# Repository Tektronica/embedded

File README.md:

# embedded

Personal embedded projects in one repository: microcontroller firmware, Raspberry Pi Python
services, shared libraries, and the KiCad design packages for the custom boards.

## Layout

| Folder                 | Contents                                                                                                       |
| ---------------------- | -------------------------------------------------------------------------------------------------------------- |
| `projects/`            | Things built to be used. Code is in `fw/` (PlatformIO) or `python/`, and `hw/` holds the KiCad package for a custom PCB. |
| `examples/<platform>/` | Single-concept demos, one self-contained firmware project each                                                 |
| `lib/<platform>/`      | Shared libraries: `arduino` for firmware, `kicad` for the symbol library                                       |
| `tools/`               | Hardware release tools: board outputs, BOM merge, printable review checklist                                   |
| `orders/`              | One folder per Digi-Key or Mouser order, holding the BOM that was bought                                       |
| `docs/`                | Cross-project notes, including `docs/hw/` for board design, part selection, and review                         |

## Projects

| Project                                          | Platform              | Custom PCB | Description                                                                                                         |
| ------------------------------------------------ | --------------------- | ---------- | ------------------------------------------------------------------------------------------------------------------- |
| [led-dimmer-4ch](projects/led-dimmer-4ch/)       | Arduino Nano          | Yes        | Four pot-controlled LED channels driven by PT4115 buck LED drivers on 12 V                                          |
| [toy-microwave](projects/toy-microwave/)         | Arduino Nano          | Yes        | Toy microwave control panel: countdown, clock, kitchen timer, 16-key keypad, and 4-digit display through an ET6226M |
| [led-dimmer-ws2812](projects/led-dimmer-ws2812/) | Arduino Nano          | No         | N-channel pot dimmer driving a WS2812 LED strip                                                                     |
| [robot-buoy](projects/robot-buoy/)               | Arduino Nano          | No         | Vertical-profiling float that dives and surfaces with a syringe ballast                                             |
| [game-dino-run](projects/game-dino-run/)         | Arduino Nano          | No         | T-Rex-Run-style game on an OLED, with the score on a 7-segment display                                              |
| [weather-station](projects/weather-station/)     | Raspberry Pi / Python | No         | Sensor collector, read-only Flask dashboard, and daily email digest, as four separate Python packages               |

## Examples

| Example                                                                   | Platform     | Demonstrates                                                                           |
| ------------------------------------------------------------------------- | ------------ | -------------------------------------------------------------------------------------- |
| [buzzer-simple](examples/arduino-nano/buzzer-simple/)                     | Arduino Nano | A passive buzzer on a button press                                                     |
| [buzzer-patterns](examples/arduino-nano/buzzer-patterns/)                 | Arduino Nano | Three buttons, each playing a different non-blocking tone pattern                      |
| [buzzer-song](examples/arduino-nano/buzzer-song/)                         | Arduino Nano | Song playback from note tables                                                         |
| [keypad](examples/arduino-nano/keypad/)                                   | Arduino Nano | A debounced 4x4 matrix keypad reader                                                   |
| [seven-segment](examples/arduino-nano/seven-segment/)                     | Arduino Nano | A 4-digit 7-segment display with static, flashing, and rolling modes                   |
| [display-keyscan-et6226m](examples/arduino-nano/display-keyscan-et6226m/) | Arduino Nano | The ET6226M display and key-scan driver on its own                                     |
| [pwm-pot-demo](examples/arduino-nano/pwm-pot-demo/)                       | Arduino Nano | A potentiometer setting PWM duty                                                       |
| [stepper](examples/arduino-nano/stepper/)                                 | Arduino Nano | A potentiometer setting stepper motor speed                                            |
| [toy-microwave-tm1637](examples/arduino-nano/toy-microwave-tm1637/)       | Arduino Nano | The earlier toy microwave on a TM1637 display and membrane keypad, kept as a reference |

## Tooling

- VS Code with the PlatformIO extension, or the `pio` CLI. No Arduino IDE.
- KiCad 10 for the custom boards.
- Wokwi for simulating examples that include a `diagram.json`.
- Python 3.12 or newer for the Raspberry Pi projects. Each one documents its own setup.

## Getting started

1. Install PlatformIO. For a VS Code-only install, put the CLI on your path:
   `export PATH="$HOME/.platformio/penv/bin:$PATH"`
2. Build any firmware from the repo root: `pio run -d projects/toy-microwave/fw`
3. Run its native unit tests: `pio test -d projects/toy-microwave/fw -e native`
4. Run every shared library's tests: `for l in lib/arduino/*/; do pio test -d "$l"; done`
5. Regenerate a board's BOM, fab, and review outputs: `tools/release.sh projects/toy-microwave/hw`

Each project and example README covers its own hardware, pins, and behavior.

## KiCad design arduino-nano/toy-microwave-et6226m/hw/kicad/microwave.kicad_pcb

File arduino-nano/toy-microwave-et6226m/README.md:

# arduino-nano/toy-microwave-et6226m

Arduino Nano firmware for a toy/prop microwave oven control panel: a countdown timer on a 4-digit
display, a turntable motor, a done/alert buzzer, a cooling fan and buzzer-tone layer for the
running "hum," an interior light, and a matrix keypad for setting time, start/stop, and the
time-of-day clock shown while idle. Display rendering and keypad scanning both go through a
single UMW ET6226M chip over one two-wire bus, rather than a separate display driver chip plus a
bit-banged matrix scan — see `arduino-nano/toy-microwave-tm1637` for that earlier approach, frozen
as a reference once this project moved to the ET6226M.

## BOM

| Qty | Role (generic) | Part chosen | Notes |
|---|---|---|---|
| 1 | 4-digit 7-segment display | Kingbright CC56-12SURKWA, common cathode | Per `hw/kicad`'s schematic (`U2`). Driven entirely through the ET6226M -- no separate display driver chip. Must be common cathode: the ET6226M's SG pins source current and its GR pins sink it. Pin-for-pin with the CA56-12 footprint. |
| 1 | Display + keypad-scan driver | UMW ET6226M (SOP-16) | Per the schematic (`U5`). Two-wire CLK/DAT to the MCU; drives the display's 4 digits and scans the 16-key matrix, sharing its GR/SG lines with the display per the schematic's `SEG_x/ROWn` and `DIG_CAn/COLn` nets. Runs in `EightSegment` mode, since `DP/KP` is wired directly to the display's shared DP line, not into the key matrix. |
| 16 | Keyswitches | Cherry MX-style (`MX1`-`MX16` in the schematic) | Diode-per-key matrix (`D1`-`D16`), `SG1-4` as rows / `GR1-4` as columns -- the same 4x4 layout and key legends (`1-9,0,*,#,A-D`) as `toy-microwave-tm1637`'s membrane keypad, just wired through the ET6226M instead of directly to the MCU. |
| 1 | Buzzer (done/alert tone, button feedback, running hum) | 12085 buzzer, 12×8.5mm, 42Ω, 3–12V | Sold in a 20-pack. Passive, electromagnetic (the 42Ω is its coil) — driven via `tone()`/PWM; also layers a quiet low-frequency tone during Running, alongside the fan and motor, for the ambient hum. |
| 1 | Buzzer driver | AO3400A (`Q2`), 100Ω gate resistor (`R9`), SS14 flyback (`D18`) | Low-side switch: the coil draws ~119mA at 5V, over the ATmega328P's 40mA pin limit. `D18` clamps the coil's turn-off spike to `+5V`. |
| 1 | Turntable motor | TYC-50 synchronous motor, 12V DC, 5–6 RPM, CW/CCW, 4W | Matches a real microwave turntable's rotation speed; its own running sound also contributes to the hum. |
| 1 | Cooling fan (running hum) | Generic 12V DC brushless fan, 40×40×10mm, sleeve bearing, ~0.08A | A commodity spec, not a specific listing — any 12V 40mm fan matches. Matches the 12V rail already used by the motor/light rather than introducing a separate 5V domain. Needs a transistor/MOSFET driver, same as the motor — not a direct GPIO connection. |
| 1 | Interior/status light | 80mm white COB LED ring ("angel eye" halo ring) | Sold in a 2-pack. 12V/24V rated — confirm current draw and how it's switched (relay/MOSFET vs. direct GPIO) before wiring. |

Motor, fan, and light are reserved, not wired. `CTRL_MOTOR`/`CTRL_FAN`/`CTRL_LIGHT` (D11, D12, D10) only
reach `J2` (pin 1 LIGHT, 2 MOTOR, 3 FAN, 4 GND), each with a 10 kΩ pull-down (`R11`-`R13`) so it reads low through
reset. They're logic-level signals for off-board peripheral boards, which own their own driver and
power. Don't connect a 12V load to `J2` directly.

## Firmware

PlatformIO project in `fw/` (`platformio.ini`, `include/`, `src/`, `test/`) built on the shared libraries in `lib/`, fully wired up:

- **`lib/SevenSeg`** — the shared 7-segment font (`encodeDigit()`, `encodeText()`, used to render "End"), `secondsToDigits()` for the MM:SS / HH:MM digit pairs, and `blinkOn()`, used to blank the display while ClockSet.
- **`Buzzer.h`** — this app's sounds (key press, done: 4 beeps, error, and the continuous Running hum) as `{frequency, duration}` step tables played by `lib/ToneSequence`. `toneStateFor()`/`isFinished()` are thin wrappers, and `isFinished()` waits for a pattern's whole sequence, not just its current on/off phase.
- **`lib/ET6226M`** — the from-scratch ET6226M driver (`ET6226M.h`, bit-banged CLK/DAT) and its hardware-free codec (`ET6226MCodec.h`: the display-control byte and key-code decoding). Shared with `arduino-nano/display-keyscan-et6226m`, the standalone project it was proven out in.
- **`lib/Debounce`** — `debounce::Debouncer<et6226m::KeyPosition>` turns the chip's raw key reading into one fresh press; `main.cpp`'s `translateKey()` maps the settled grid/segment to an `Event`.
- **`lib/WallClock`** — the time-of-day `Clock`, the countdown `Timer`, and the digit-entry helpers `Microwave.h` builds on. It's a software clock, so it resets to 0:00 on every power loss or reset; surviving a power cycle needs a battery-backed RTC.
- **`Microwave.h`** — the app-level orchestrator: the Idle → Setting → Running → Done countdown state machine (plus `ClockSet`, reachable from Idle), driven by abstract `Event`s (`Digit`/`Start`/`Cancel`/`Clock`/`Timer`/`Tick`) rather than any specific keypad wiring. Setting/Running/Done serve two `Function`s — `CookTime` and `Timer` (a plain kitchen timer) — sharing one flow rather than duplicating it, since digit entry, Start/Cancel, and counting down to Done are identical either way; `isCooking()` (`Running` + `Function::CookTime`) is the only thing that distinguishes them, and it's what `main.cpp` gates the motor/fan/light/hum on. Delegates time-of-day keeping and countdown-counting to `lib/WallClock`'s `wallclock::Clock`/`wallclock::Timer` rather than absorbing either concern directly. Unchanged by the ET6226M migration — this state machine never touched the display or keypad hardware directly.
- **`main.cpp`** — reads the ET6226M's key code → debounces → decodes to grid/segment → `Event` → state machine → buzzer pattern selection, motor/fan/light on/off, and ET6226M display rendering (colon included, via the DP bit on `COLON_DIGIT_INDEX`'s grid -- the same trick `toy-microwave-tm1637` used with TM1637's DP bit).
- Motor, fan, and light have no dedicated header — all three are plain on/off hardware glue in `main.cpp`.

### Behavior

- **Idle** — displays the live time-of-day clock (HH:MM, 12-hour — the clock is kept internally as 24-hour and converted for display; no AM/PM indicator on this display, so e.g. 8:15 looks the same whether it's AM or PM). A digit key starts entering a cook time; `B` starts entering a kitchen timer; `A` starts entering a new clock time.
- **Setting** — entering a countdown digit-by-digit (MM:SS, calculator-style: each press appends to the low end and shifts existing digits left, e.g. `3` → `0:03`, `30` → `0:30`, `300` → `3:00`), for whichever `Function` was selected to get here (`CookTime` via a digit key, `Timer` via `B`). `#` starts the countdown if a nonzero time is entered; `*` cancels back to Idle.
- **Running** — counts down once per second. If this countdown is `CookTime`, the motor, fan, and light are on, plus the ambient hum; a `Timer` (kitchen timer) countdown runs silently in the background with none of that hardware on. `*` cancels back to Idle at any point, ending a cook or a timer the same way.
- **Done** — countdown reached 0:00; the display shows "End" (no colon) instead of a static "0:00", whether it was a cook or a kitchen timer. Buzzer plays a 4-beep done pattern and repeats every 10 seconds as a reminder for as long as Done goes unacknowledged. The display flashes in exact sync with each beep of that pattern — dark whenever the buzzer is silent between beeps, lit whenever it's sounding — and stays steady during the quiet gap between reminders. Any key returns to Idle.
- **ClockSet** — entering a new time-of-day, HH:MM, same calculator-style digit entry as a countdown, typed in 24-hour form (e.g. `1930` for 7:30 PM). The whole display flashes for as long as ClockSet is active, so editing the clock is visually distinct from just reading it. While typing, the live preview clamps hours to 23 and minutes to 59; `#` only confirms and returns to Idle if the entered hour:minute is actually a valid 24-hour time (e.g. `2400` is refused, not silently clamped to 23:00) — otherwise it's a no-op and entry continues. `*` cancels, discarding the entry and leaving the clock unchanged.
- The clock keeps advancing in the background in every state except while it's actively being set (cooking or timing doesn't stop the time of day).

### 4x4 keypad mapping

| Key(s) | Action |
|---|---|
| `0`-`9` | Enter a digit (cook time or kitchen timer while Idle/Setting, clock time while ClockSet) |
| `#` | Start / confirm (starts the countdown from Setting; confirms the new clock time from ClockSet) |
| `*` | Cancel (back to Idle, discarding whatever was being entered, or ending a running countdown) |
| `A` | Clock — from Idle, begin setting the time-of-day clock |
| `B` | Timer — from Idle, begin entering a plain kitchen timer (counts down and beeps; doesn't turn on the motor/fan/light) |
| `C` | +30 s — from Idle, start a 30-second cook; while Running, add 30 s to the cook or timer countdown (caps at 99:59) |
| `D` | Mute — toggle all buzzer sound in any state; resets to sound on at power-up |

`main.cpp`'s `translateKey()` maps each key legend onto its confirmed
`(grid, segment)` scan position (`hw/kicad`'s schematic: `SG1-4`=rows, `GR1-4`=columns) --
this LAYOUT table is the only place a different physical keycap arrangement would need updating;
the electrical wiring stays the same regardless of which legend is assigned where.

**Driver**: `lib/ET6226M`, a from-scratch driver (no Arduino library exists for this chip). The colon (`COLON_DIGIT_INDEX`/`COLON_BIT` in `main.cpp`)
uses the same DP-bit-on-one-grid trick `toy-microwave-tm1637` used with TM1637, confirmed against
the schematic rather than guessed — the Kingbright display's shared DP line is wired straight to
the ET6226M's `DP/KP` pin (`EightSegment` mode).

Pin assignments, per `hw/kicad`: ET6226M `CLK`/`DAT` on D8/D9, buzzer D6, motor D11, fan
D12, light D10 (not D13, whose onboard LED the bootloader blinks at reset). The old TM1637 approach's 8 matrix row/column pins are gone entirely — the keypad
is scanned by the ET6226M, not the MCU.

## Folders

- **`fw/`** — firmware, a self-contained PlatformIO project (details under Firmware above).
- **`hw/`** — the board's design package, laid out per `kicad/README.md`: KiCad project in
  `hw/kicad/`, datasheets in `hw/datasheets/`, the Onshape enclosure template in
  `hw/mech/enclosure-template.dxf`, and generated `bom/`, `fab/`, and `review/` outputs.
- **`docs/`** — design notes: the buck converter change and the ET6226M wiring diagram.

## Quick start

Requires [PlatformIO](https://platformio.org/) (VSCode extension or CLI) — no Arduino IDE needed.
If `pio` isn't on your shell `PATH` (VSCode-extension-only installs), add it:

```bash
export PATH="$HOME/.platformio/penv/bin:$PATH"
```

```bash
cd arduino-nano/toy-microwave-et6226m/fw
pio run                 # build
pio run -t upload       # build + flash the Nano
pio device monitor      # serial monitor
pio test -e native      # off-device unit tests
```

## Simulate (Wokwi)

Not available — the ET6226M isn't a part Wokwi supports.

## Status

Schematic exists (`hw/kicad`): ET6226M-driven display and 16-key diode matrix, Arduino
Nano module. Firmware logic is implemented and tested (38 unit tests across `Buzzer.h` and `Microwave.h`,
plus each shared library's own tests) against that schematic, but not yet run on real hardware.

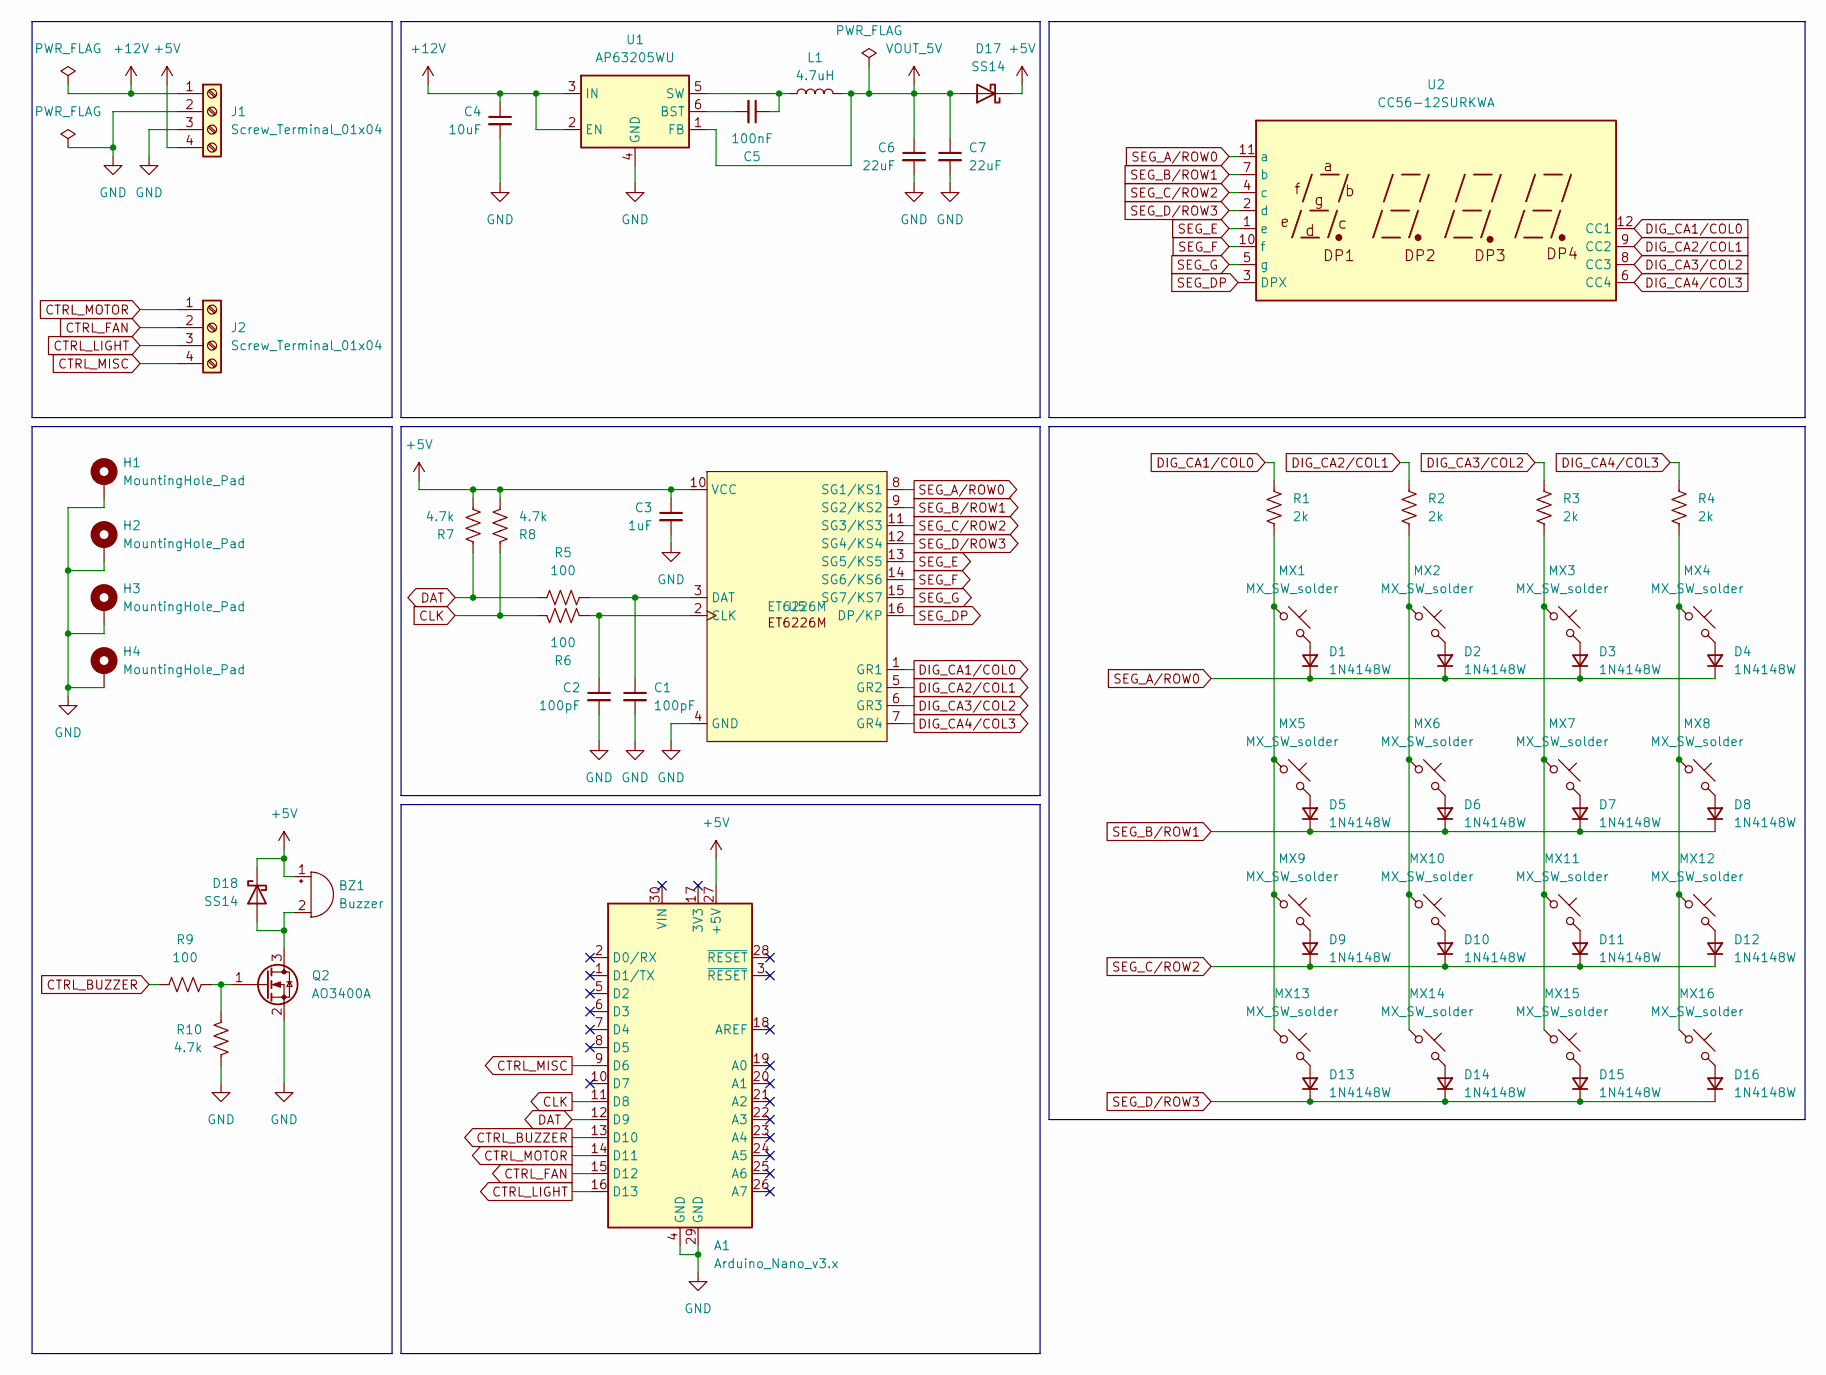
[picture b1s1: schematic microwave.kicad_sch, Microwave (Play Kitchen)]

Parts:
A1: Arduino_Nano_v3.x; Arduino_Nano
BZ1: Buzzer; Buzzer_12x9.5RM7.6; MPN WT-1205; Digi-Key 433-1028-ND
C1, C2: 100pF; C_0805_2012Metric_Pad1.18x1.45mm_HandSolder; MPN C0805C101J1GAC7210; Digi-Key 399-C0805C101J1GAC7210CT-ND
C3: 1uF; C_0805_2012Metric_Pad1.18x1.45mm_HandSolder; MPN C0805C105K3RACAUTO; Digi-Key 399-6929-1-ND
C4: 10uF; C_1210_3225Metric_Pad1.33x2.70mm_HandSolder; MPN TMK325AB7106MMHPR; Digi-Key 587-TMK325AB7106MMHPRCT-ND
C5: 100nF; C_0805_2012Metric_Pad1.18x1.45mm_HandSolder; MPN C0805C104M5RACAUTO; Digi-Key 399-12977-1-ND
C6, C7: 22uF; C_1210_3225Metric_Pad1.33x2.70mm_HandSolder; MPN CL32A226MAJNNNE; Digi-Key 1276-3373-1-ND
D1, D2, D3, D4, D5, D6, D7, D8, D9, D10, D11, D12, D13, D14, D15, D16: 1N4148W; D_SOD-123; MPN 1N4148W-7-F; Digi-Key 1N4148W-FDICT-ND
D17, D18: SS14; D_SMA; MPN SS14-E3/61T; Digi-Key SS14-E3/61TGICT-ND
H1, H2, H3, H4: MountingHole_Pad; MountingHole_3.2mm_M3_ISO7380_Pad_TopBottom
J1, J2: Screw_Terminal_01x04; TerminalBlock_Phoenix_MKDS-1,5-4-5.08_1x04_P5.08mm_Horizont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; MPN 1715747; Digi-Key 277-1265-ND
L1: 4.7uH; L_Murata_LQH55DN_5.7x5.0mm; MPN LQH55DN4R7M03L; Digi-Key 490-LQH55DN4R7M03LCT-ND
MX1, MX2, MX3, MX4, MX5, MX6, MX7, MX8, MX9, MX10, MX11, MX12, MX13, MX14, MX15, MX16: MX_SW_solder; SW_MX_1u
Q2: AO3400A; SOT-23; MPN AO3400A; Digi-Key 785-1000-1-ND
R1, R2, R3, R4: 2k; R_0805_2012Metric_Pad1.20x1.40mm_HandSolder; MPN RC0805FR-072KL; Digi-Key 311-2.00KCRCT-ND
R5, R6, R9: 100; R_0805_2012Metric_Pad1.20x1.40mm_HandSolder; MPN RC0805FR-07100RL; Digi-Key 311-100CRCT-ND
R7, R8, R10: 4.7k; R_0805_2012Metric_Pad1.20x1.40mm_HandSolder; MPN RC0805FR-074K7L; Digi-Key 311-4.70KCRCT-ND
U1: AP63205WU; TSOT-23-6; MPN AP63205WU-7; Digi-Key AP63205WU-7DICT-ND
U2: CC56-12SURKWA; CA56-12SURKWA; MPN CC56-12SURKWA; Digi-Key 754-CC56-12SURKWA-ND
U5: ET6226M; SOP-16_4.4x10.4mm_P1.27mm; MPN ET6226M; Digi-Key 4518-ET6226MCT-ND

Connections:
+5V: A1.27 (+5V), BZ1.1 (+), C3.1, D17.1 (K), D18.1 (K), J1.4, R7.1, R8.1, U5.10 (VCC)
+12V: C4.1, J1.1, U1.2 (EN), U1.3 (IN)
CLK: A1.11 (D8), R6.1, R8.2
CTRL_BUZZER: A1.13 (D10), R9.1
CTRL_FAN: A1.15 (D12), J2.2
CTRL_LIGHT: A1.16 (D13), J2.3
CTRL_MISC: A1.9 (D6), J2.4
CTRL_MOTOR: A1.14 (D11), J2.1
DAT: A1.12 (D9), R5.1, R7.2
DIG_CA1/COL0: R1.1, U2.12 (CC1), U5.1 (GR1)
DIG_CA2/COL1: R2.1, U2.9 (CC2), U5.5 (GR2)
DIG_CA3/COL2: R3.1, U2.8 (CC3), U5.6 (GR3)
DIG_CA4/COL3: R4.1, U2.6 (CC4), U5.7 (GR4)
GND: A1.4 (GND), A1.29 (GND), C1.2, C2.2, C3.2, C4.2, C6.2, C7.2, H1.1, H2.1, H3.1, H4.1, J1.2, J1.3, Q2.2 (S), R10.1, U1.4 (GND), U5.4 (GND)
unnamed: BZ1.2 (-), D18.2 (A), Q2.3 (D)
unnamed: D1.2 (A), MX1.2
unnamed: D2.2 (A), MX2.2
unnamed: D3.2 (A), MX3.2
unnamed: D4.2 (A), MX4.2
unnamed: D5.2 (A), MX5.2
unnamed: D6.2 (A), MX6.2
unnamed: D7.2 (A), MX7.2
unnamed: D8.2 (A), MX8.2
unnamed: D9.2 (A), MX9.2
unnamed: D10.2 (A), MX10.2
unnamed: D11.2 (A), MX11.2
unnamed: D12.2 (A), MX12.2
unnamed: D13.2 (A), MX13.2
unnamed: D14.2 (A), MX14.2
unnamed: D15.2 (A), MX15.2
unnamed: D16.2 (A), MX16.2
unnamed: MX1.1, MX5.1, MX9.1, MX13.1, R1.2
unnamed: MX2.1, MX6.1, MX10.1, MX14.1, R2.2
unnamed: MX3.1, MX7.1, MX11.1, MX15.1, R3.2
unnamed: MX4.1, MX8.1, MX12.1, MX16.1, R4.2
unnamed: Q2.1 (G), R9.2, R10.2
unnamed: C5.2, U1.6 (BST)
unnamed: C5.1, L1.1, U1.5 (SW)
unnamed: C2.1, R6.2, U5.2 (CLK)
unnamed: C1.1, R5.2, U5.3 (DAT)
SEG_A/ROW0: D1.1 (K), D2.1 (K), D3.1 (K), D4.1 (K), U2.11 (a), U5.8 (SG1/KS1)
SEG_B/ROW1: D5.1 (K), D6.1 (K), D7.1 (K), D8.1 (K), U2.7 (b), U5.9 (SG2/KS2)
SEG_C/ROW2: D9.1 (K), D10.1 (K), D11.1 (K), D12.1 (K), U2.4 (c), U5.11 (SG3/KS3)
SEG_DP: U2.3 (DPX), U5.16 (DP/KP)
SEG_D/ROW3: D13.1 (K), D14.1 (K), D15.1 (K), D16.1 (K), U2.2 (d), U5.12 (SG4/KS4)
SEG_E: U2.1 (e), U5.13 (SG5/KS5)
SEG_F: U2.10 (f), U5.14 (SG6/KS6)
SEG_G: U2.5 (g), U5.15 (SG7/KS7)
VOUT_5V: C6.1, C7.1, D17.2 (A), L1.2, U1.1 (FB)

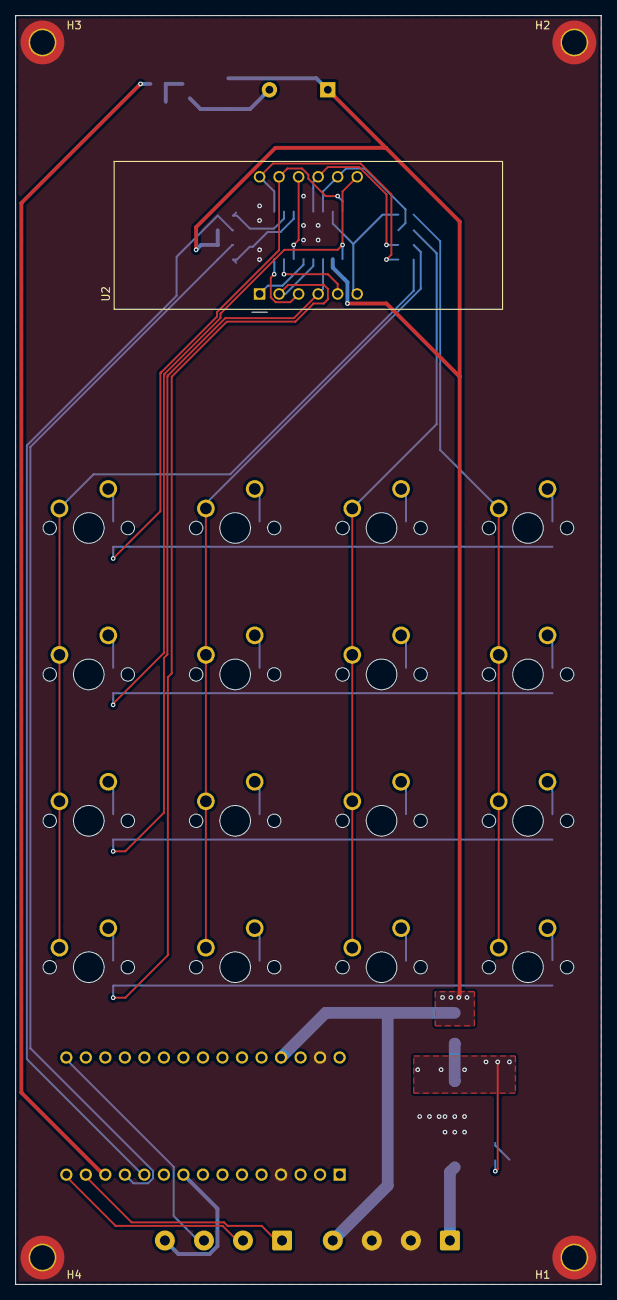
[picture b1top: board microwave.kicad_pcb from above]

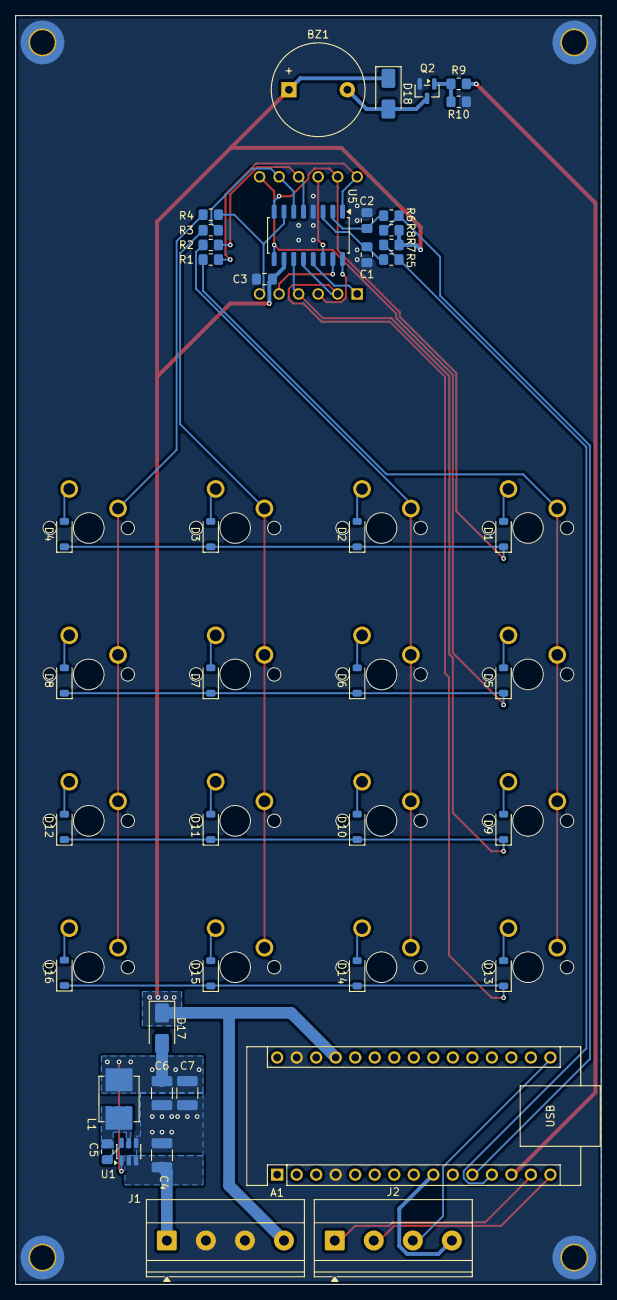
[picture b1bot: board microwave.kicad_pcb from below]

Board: 2 copper layers, 76.2 x 165.1 mm, 64 parts (43 on the bottom side), 49 nets.

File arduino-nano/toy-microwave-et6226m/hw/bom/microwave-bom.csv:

"Reference","Qty","Value","Footprint","MPN","Manufacturer","Digi-Key","Mouser","LCSC"
"BZ1","1","Buzzer","Buzzer_Beeper:Buzzer_12x9.5RM7.6","WT-1205","Soberton Inc.","433-1028-ND","",""
"C1,C2","2","100pF","Capacitor_SMD:C_0805_2012Metric_Pad1.18x1.45mm_HandSolder","C0805C101J1GAC7210","KEMET","399-C0805C101J1GAC7210CT-ND","80-C0805C101J1G7210",""
"C3","1","1uF","Capacitor_SMD:C_0805_2012Metric_Pad1.18x1.45mm_HandSolder","C0805C105K3RACAUTO","KEMET","399-6929-1-ND","80-C0805C105K3RAUTO",""
"C4","1","10uF","Capacitor_SMD:C_1210_3225Metric_Pad1.33x2.70mm_HandSolder","TMK325AB7106MMHPR","Taiyo Yuden","587-TMK325AB7106MMHPRCT-ND","963-TMK325AB7106MMPR",""
"C5","1","100nF","Capacitor_SMD:C_0805_2012Metric_Pad1.18x1.45mm_HandSolder","C0805C104M5RACAUTO","KEMET","399-12977-1-ND","80-C0805C104M5RAUTO",""
"C6,C7","2","22uF","Capacitor_SMD:C_1210_3225Metric_Pad1.33x2.70mm_HandSolder","CL32A226MAJNNNE","Samsung","1276-3373-1-ND","187-CL32A226MAJNNNE",""
"D1-D16","16","1N4148W","Diode_SMD:D_SOD-123","1N4148W-7-F","Diodes Inc","1N4148W-FDICT-ND","621-1N4148W-F",""
"D17,D18","2","SS14","Diode_SMD:D_SMA","SS14-E3/61T","Vishay","SS14-E3/61TGICT-ND","625-SS14-E3",""
"J1,J2","2","Screw_Terminal_01x04","TerminalBlock_Phoenix:TerminalBlock_Phoenix_MKDS-1,5-4-5.08_1x04_P5.08mm_Horizontal","1715747","Phoenix Contact","277-1265-ND","651-1715747",""
"L1","1","4.7uH","Inductor_SMD:L_Murata_LQH55DN_5.7x5.0mm","LQH55DN4R7M03L","Murata","490-LQH55DN4R7M03LCT-ND","81-LQH55DN4R7M03L",""
"Q2","1","AO3400A","Package_TO_SOT_SMD:SOT-23","AO3400A","Alpha & Omega","785-1000-1-ND","",""
"R1-R4","4","2k","Resistor_SMD:R_0805_2012Metric_Pad1.20x1.40mm_HandSolder","RC0805FR-072KL","Yageo","311-2.00KCRCT-ND","603-RC0805FR-072KL",""
"R5,R6,R9","3","100","Resistor_SMD:R_0805_2012Metric_Pad1.20x1.40mm_HandSolder","RC0805FR-07100RL","Yageo","311-100CRCT-ND","603-RC0805FR-07100RL",""
"R7,R8,R10","3","4.7k","Resistor_SMD:R_0805_2012Metric_Pad1.20x1.40mm_HandSolder","RC0805FR-074K7L","Yageo","311-4.70KCRCT-ND","603-RC0805FR-074K7L",""
"U1","1","AP63205WU","Package_TO_SOT_SMD:TSOT-23-6","AP63205WU-7","Diodes Inc","AP63205WU-7DICT-ND","621-AP63205WU-7",""
"U2","1","CC56-12SURKWA","Display_7Segment:CA56-12SURKWA","CC56-12SURKWA","Kingbright","754-CC56-12SURKWA-ND","604-CC5612SURKWA",""
"U5","1","ET6226M","Package_SO:SOP-16_4.4x10.4mm_P1.27mm","ET6226M","UMW","4518-ET6226MCT-ND","",""

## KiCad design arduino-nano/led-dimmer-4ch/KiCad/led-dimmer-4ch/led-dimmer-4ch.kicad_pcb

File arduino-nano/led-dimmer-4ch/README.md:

# arduino-nano/led-dimmer-4ch

A 4-channel potentiometer-controlled LED dimmer board: Arduino Nano + 4× PT4115 constant-current
buck LED drivers, powered from 12V (Nano runs off 5V via an onboard AP63205 buck regulator, or
from its own USB port). Each channel is one off-board pot (A0–A3, wired in through `J4`/`J5`) →
one PWM output (D9, D10, D3, D11) → one PT4115's DIM pin. USB alone powers the Nano only: the
PT4115s need at least 6V on VIN.

## PWM pins (ATmega328P)

The Nano's 6 PWM-capable pins split across 3 timers, each with its own default `analogWrite()`
frequency:

| Timer | Pins | Frequency |
|---|---|---|
| Timer0 | D5, D6 | ~980 Hz (also drives `millis()`/`delay()`) |
| Timer1 | D9, D10 | ~490 Hz |
| Timer2 | D3, D11 | ~490 Hz |

This board uses D9, D10, D3, D11 (Timer1 + Timer2), skipping D5/D6 so all 4 channels share one
common ~490 Hz frequency with zero timer register configuration.

## Folders

- **`hw/`** — the board's design package, laid out per `kicad/README.md`: KiCad project in
  `hw/kicad/`, datasheets in `hw/datasheets/`, and generated `bom/`, `fab/`, and `review/`
  outputs. The 5V buck block (`U5`, `C5`-`C8`, `D5`, `L5`) is the same layout as
  `toy-microwave-et6226m`'s, mirrored to the front side. The LM2596 datasheets are from the board's
  earlier buck regulator. The AP63205's lives in `toy-microwave-et6226m/hw/datasheets/`.
- **`fw/`** — firmware, a self-contained PlatformIO project. Includes a Wokwi diagram substituting
  plain LED+resistor pairs for the PT4115 modules, to verify the 4-channel PWM/pot correspondence
  without real hardware.

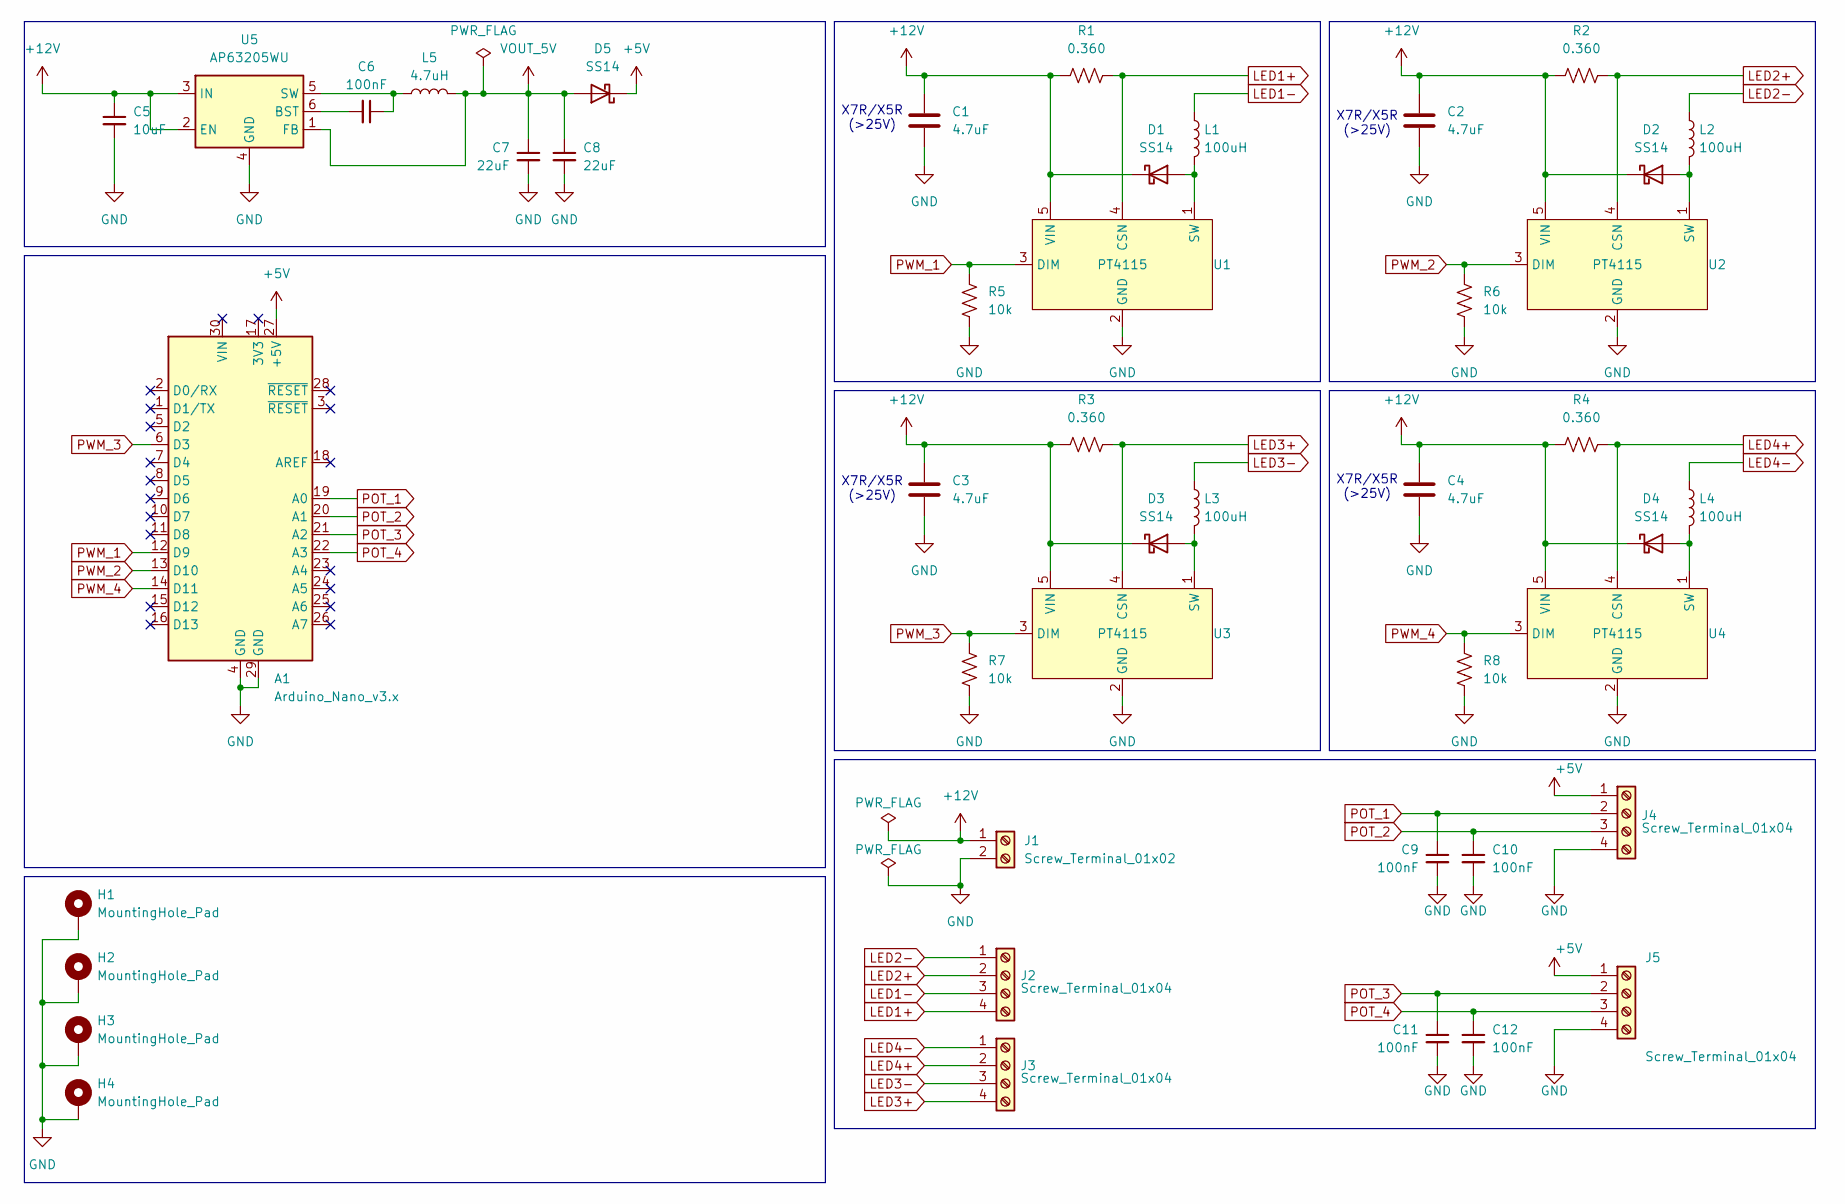
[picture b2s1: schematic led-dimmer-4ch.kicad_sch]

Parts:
A1: Arduino_Nano_v3.x; Arduino_Nano
C1, C2, C3, C4: 4.7uF; C_1210_3225Metric_Pad1.33x2.70mm_HandSolder
C5: 10uF; C_1210_3225Metric_Pad1.33x2.70mm_HandSolder
C6, C9, C10, C11, C12: 100nF; C_0805_2012Metric_Pad1.18x1.45mm_HandSolder
C7, C8: 22uF; C_1210_3225Metric_Pad1.33x2.70mm_HandSolder
D1, D2, D3, D4, D5: SS14; D_SMA
H1, H2, H3, H4: MountingHole_Pad; MountingHole_3.2mm_M3_Pad_Via
J1: Screw_Terminal_01x02; TerminalBlock_Phoenix_MKDS-1,5-2-5.08_1x02_P5.08mm_Horizont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
J2, J3, J4, J5: Screw_Terminal_01x04; TerminalBlock_Phoenix_MKDS-1,5-4-5.08_1x04_P5.08mm_Horizont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
L1, L2, L3, L4: 100uH; L_Coilcraft_MSS1038-XXX
L5: 4.7uH; L_Murata_LQH55DN_5.7x5.0mm
R1, R2, R3, R4: 0.360; R_0805_2012Metric_Pad1.20x1.40mm_HandSolder
R5, R6, R7, R8: 10k; R_0805_2012Metric_Pad1.20x1.40mm_HandSolder
U1, U2, U3, U4: PT4115; SOT-89-5_Handsoldering
U5: AP63205WU; TSOT-23-6

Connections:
+5V: A1.27 (+5V), D5.1 (K), J4.1, J5.1
+12V: C1.1, C2.1, C3.1, C4.1, C5.1, D1.1 (K), D2.1 (K), D3.1 (K), D4.1 (K), J1.1, R1.1, R2.1, R3.1, R4.1, U1.5 (VIN), U2.5 (VIN), U3.5 (VIN), U4.5 (VIN), U5.2 (EN), U5.3 (IN)
GND: A1.4 (GND), A1.29 (GND), C1.2, C2.2, C3.2, C4.2, C5.2, C7.2, C8.2, C9.2, C10.2, C11.2, C12.2, H1.1 (1_1), H2.1 (1_1), H3.1 (1_1), H4.1 (1_1), J1.2, J4.4, J5.4, R5.2, R6.2, R7.2, R8.2, U1.2 (GND), U2.2 (GND), U3.2 (GND), U4.2 (GND), U5.4 (GND)
LED1+: J2.4, R1.2, U1.4 (CSN)
LED1-: J2.3, L1.1
LED2+: J2.2, R2.2, U2.4 (CSN)
LED2-: J2.1, L2.1
LED3+: J3.4, R3.2, U3.4 (CSN)
LED3-: J3.3, L3.1
LED4+: J3.2, R4.2, U4.4 (CSN)
LED4-: J3.1, L4.1
unnamed: D1.2 (A), L1.2, U1.1 (SW)
unnamed: D2.2 (A), L2.2, U2.1 (SW)
unnamed: D3.2 (A), L3.2, U3.1 (SW)
unnamed: D4.2 (A), L4.2, U4.1 (SW)
unnamed: C6.2, U5.6 (BST)
unnamed: C6.1, L5.1, U5.5 (SW)
POT_1: A1.19 (A0), C9.1, J4.2
POT_2: A1.20 (A1), C10.1, J4.3
POT_3: A1.21 (A2), C11.1, J5.2
POT_4: A1.22 (A3), C12.1, J5.3
PWM_1: A1.12 (D9), R5.1, U1.3 (DIM)
PWM_2: A1.13 (D10), R6.1, U2.3 (DIM)
PWM_3: A1.6 (D3), R7.1, U3.3 (DIM)
PWM_4: A1.14 (D11), R8.1, U4.3 (DIM)
VOUT_5V: C7.1, C8.1, D5.2 (A), L5.2, U5.1 (FB)

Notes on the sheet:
X7R/X5R (>25V)

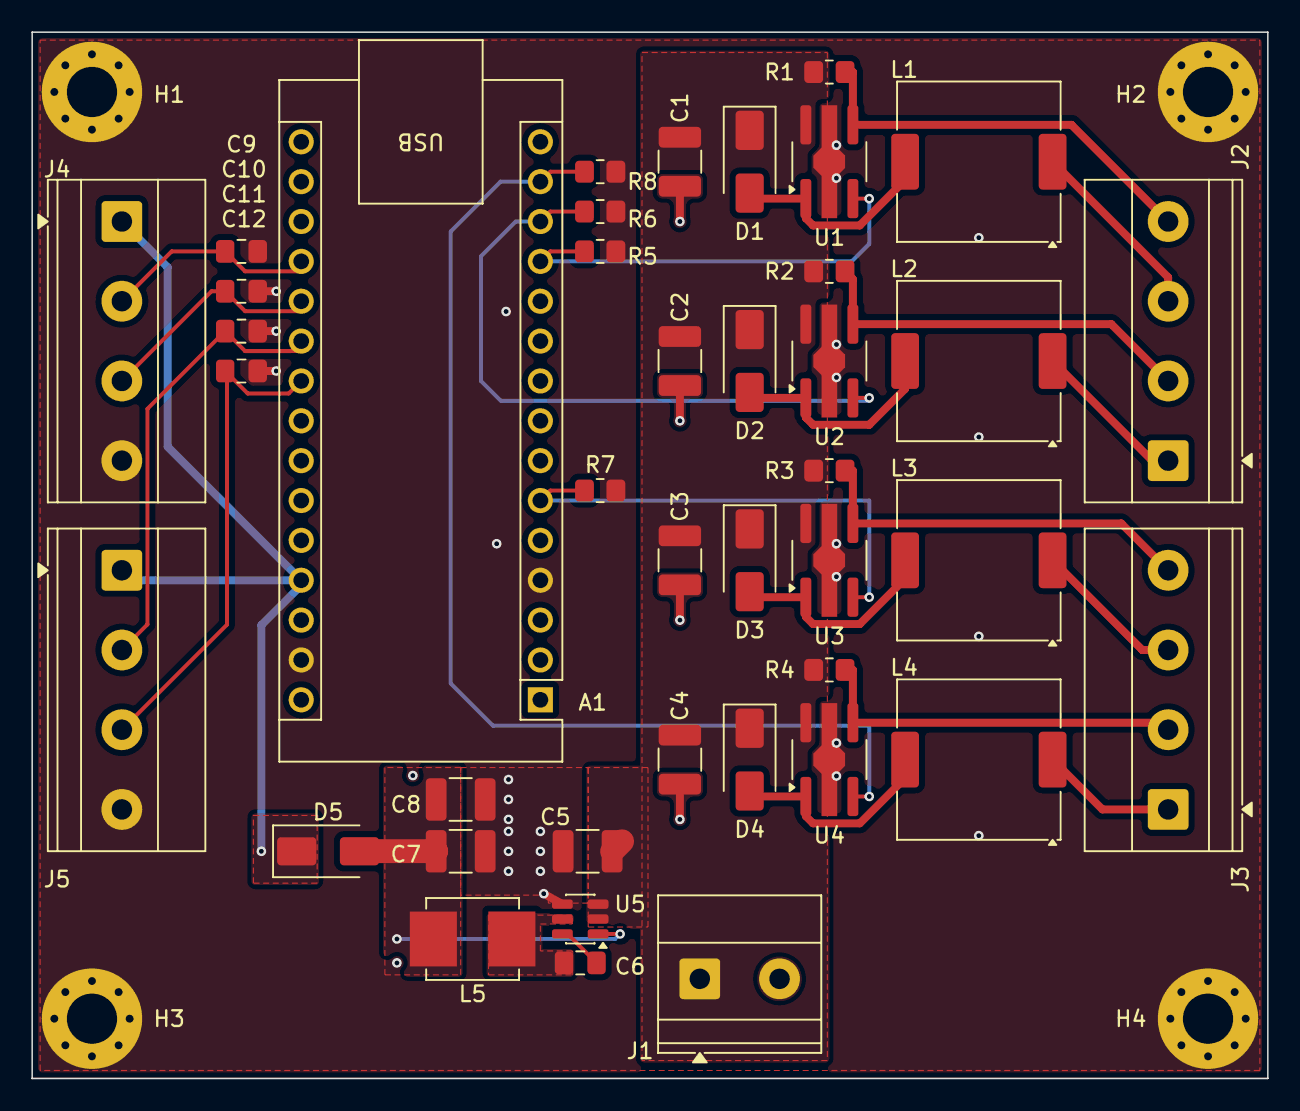
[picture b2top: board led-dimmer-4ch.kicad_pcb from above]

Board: 2 copper layers, 78.7 x 66.7 mm, 45 parts (0 on the bottom side), 26 nets.

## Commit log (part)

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2026-06-23 chore: scaffold repo config and commit tooling
    - What: added .gitignore, a project CLAUDE.md, and a /commit slash command
    - Why: a new repo needs ignore rules, pinned project context, and a firmware-tuned commit flow
    - How: PlatformIO-oriented .gitignore with a secrets block; CLAUDE.md capturing hardware/architecture/naming rules; .claude/commands/commit.md adapted from the web template to pio/C++
    - Benefit: consistent ignores, auto-loaded context each session, and a repeatable commit process
2026-06-23 docs: add project README and pillar documentation
    - What: added the root README and docs/ pillars (setup, hardware, architecture, appliances)
    - Why: capture the design before writing firmware — concept, power budget, MVC + IAppliance plugin, naming schema
    - How: README as the GitHub landing page linking into docs/; one README per pillar holding the detail
    - Benefit: the design and decisions are documented and discoverable from the first commit
2026-06-24 chore: update project rules for rename + personal repo
    - What: refreshed CLAUDE.md and the /commit command for the fw-nano-playKitchen rename and personal ownership
    - Why: repo was renamed (board-led schema) and it's a personal Tektronica repo, not Fluke property
    - How: updated naming/build notes in CLAUDE.md; removed the Fluke copyright-header check from /commit and CLAUDE.md
    - Benefit: project instructions and commit flow match the repo's real identity and ownership
2026-06-24 test: add native unit tests for model and pure logic
    - What: added test_model (HobModel) and test_logic (HeatRamp, InputMap) Unity suites
    - Why: validate the pure logic off-device with no hardware needed
    - How: native PlatformIO env running Unity; assert clamping, defaults, ADC mapping, EMA convergence, and the heat-color ramp
    - Benefit: 9 passing tests guard core behavior; runnable via `pio test -e native`
2026-06-24 docs: rename to fw-nano-playKitchen, restructure, add troubleshooting
    - What: updated all docs to the new name/schema and MVC lib layout, and added docs/troubleshooting entries
    - Why: the repo was renamed and the firmware reorganized by MVC; the Zscaler/PlatformIO setup gotchas needed recording
    - How: refreshed README + pillar docs with the new structure tree and test command; wrote two troubleshooting writeups (SSL cert verify, blocked package mirror)
    - Benefit: docs match the code, and the environment fixes are captured for next time
2026-06-24 build: make native test-only, fix pio run, set old-bootloader upload speed
    - What: added [platformio] default_envs=nano, excluded src/ from the native env, and set board_upload.speed=57600
    - Why: `pio run`/VSCode Build was compiling the Arduino firmware on the host (native) and failing on Arduino.h; the ELEGOO Nano (CH340) uses the old bootloader
    - How: default_envs targets nano for builds; native is reserved for `pio test -e native` via build_src_filter; 57600 is the old-bootloader upload speed
    - Benefit: `pio run` and VSCode Build are clean (nano only); native unit tests still run; upload config matches this board (pending the CH340 auto-reset/driver fix to actually flash)
2026-06-24 chore: gitignore Claude Code local settings
    - What: ignore .claude/settings.local.json
    - Why: it holds machine-specific permission rules (absolute paths) and is personal, not team config
    - How: added the path under the existing ignore list
    - Benefit: local Claude permissions stay out of version control
2026-06-24 refactor: collapse to two source files, drop the plugin layer
    - What: replaced the lib/ MVC class tree + IAppliance/CooktopAppliance plugin with include/Cooktop.h (all pure logic) + src/main.cpp (Arduino glue); merged the two test suites into test_cooktop; upda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
    - Why: ~200 lines spread across 13 files was over-built for a single-appliance toy — the plugin seam was premature abstraction
    - How: kept the one seam that earns its keep (pure logic vs hardware, so tests still run off-device); MVC survives as the read→update→render loop in main; the plugin layout is preserved in git histor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
    - Benefit: the firmware reads in two
2026-06-24 docs: add Wokwi simulation setup (VS Code)
    - What: added docs/simulation pillar plus wokwi.toml and diagram.json; refreshed doc indexes and post-refactor wording
    - Why: lets us verify the 4-dimmer→4-hob behavior in the simulator with no hardware, running the real compiled binary
    - How: wokwi.toml points at .pio/build/nano/firmware.elf; diagram.json wires 4 pots (A0–A3) + 4×35 rings (D6); doc covers the license flow, run steps, and wiring
    - Benefit: hardware-free end-to-end check; docs reflect the two-file structure (no more IAppliance references)
2026-06-24 fix(sim): make Wokwi diagram light up and tidy it
    - What: set non-zero potentiometer values, switched LED strips to pixelSize 2020, kept verified pins
    - Why: strips rendered all-black (pot value defaults to 0 → level 0 → off) and were ~800px wide (default 5050 size) — looked broken
    - How: pots seeded 1000/650/350/120 so the 4 strips show distinct heat colors on load; compact 2020 pixels; power from Nano 5V/GND.1/GND.2, data chained D6→DIN→DOUT
    - Benefit: simulator now visibly proves the 4-dimmer→4-hob mapping; documented the all-black gotcha
2026-06-24 fix(sim): use nano:6 data pin label and ground all 4 strips
    - What: dropped the dead nano:D6 data wire (kept nano:6 → ring1:DIN), added ring4:VSS ground; documented the pin-label gotcha
    - Why: the strips stayed black because wokwi-arduino-nano's digital pin is labeled "6", not "D6" — "D6" silently fails to connect, so no data reached the LEDs
    - How: data is nano:6 → ring1:DIN → chained DOUT/DIN; power VDD→5V and VSS→GND.1 on all four strips
    - Benefit: the simulator now lights the four hobs in distinct heat colors, verifying the 4-dimmer→4-hob mapping
2026-06-24 refactor(cooktop): simplify render color assignment
    - What: replaced the ternary `CRGB(...) : CRGB(CHSV(...))` with a default-black + conditional assign
    - Why: clearer to read, and sidesteps an IntelliSense false-positive ("ambiguous conversion to CRGB") on the ternary
    - How: CRGB color = CRGB::Black; if (c.v != 0) color = CHSV(...);
    - Benefit: same behavior/build, easier to read
2026-06-24 refactor: genericize to an N-channel LED-strip dimmer controller
    - What: removed kitchen/hob/cooktop vocabulary from the code — namespace cooktop→controller, HobModel→Levels, heatColor→levelColor, header Cooktop.h→LEDStripDimmer.h; consts renamed to prefix/broad→n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
    - Why: the firmware is a generic dimmer-input → LED-strip-output mechanism; the application (a toy kitchen) must not dictate the design's vocabulary
    - How: pure logic in LEDStripDimmer.h (named to avoid FastLED's controller.h clash on case-insensitive FS); Arduino glue in main.cpp; comments use "dimmer inputs"/"LED strip ou
2026-06-24 docs: sync status + setup with reality
    - What: status now says the current build is flashed/running on the Nano with behavior verified in Wokwi (no longer implying an older build); setup snippet notes FastLED-from-GitHub and points at the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
    - Why: docs must match implementation — the current generic/red→orange build is now flashed, and the "starting point" snippet diverged from the actual config
    - How: reworded status in README + docs/README; annotated the setup platformio.ini example
    - Benefit: no overclaim; docs and the running firmware agree
2026-06-24 docs(code): note FastLED rainbow hue map in levelColor
    - What: comment explaining hue values are read by FastLED's rainbow map (0=red, 32=orange, 64=yellow) and that capping at 32 keeps it red→orange
    - Why: 32 was a magic number; FastLED's HUE_* names can't be used here (header is hardware-free for testing)
    - How: comment-only; behavior unchanged
    - Benefit: the curve's color intent is self-documenting
2026-06-24 feat(curve): shift heat curve to orange-red (hue cap 32→16)
    - What: levelColor hue now caps at 16 (orange-red) instead of 32 (orange); test + docs updated
    - Why: at 32 the hottest read as plain orange; wanted orange-red / blood-red, i.e. red-dominant
    - How: hue = t*16/254 (FastLED rainbow: 0=red, 16≈orange-red, 32=orange); documented the cap as a tuning knob (toward 0 = bloodier red); test asserts hue <= 16
    - Benefit: hobs glow red→orange-red like a heating element; build + 10/10 tests pass
2026-06-24 feat: optional mode + color switches (animations + palettes)
    - What: two optional push switches cycle a Mode enum (Solid/Blink/Strobe/Chase) and a Palette enum (HeatRedOrange/Green/Blue/White/Rainbow); render is now a pure per-pixel pixelColor(palette,mode,lev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
    - Why: requested — switchable animations + colors, defaulting to red-orange/solid when the switches aren't wired
    - How: switch pins use INPUT_PULLUP so an unwired pin reads HIGH and never cycles (default holds); Rainbow spans one hue cycle per LED strip; dimmer level still = brightness; all logic stays hardware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
2026-06-24 docs: document mode/color switches, palettes, and pixelColor
    - What: README/docs/architecture/hardware/simulation now cover the two optional switches (D2 mode, D3 color), the Palette/Mode enums, pixelColor, and the Wokwi pushbuttons
    - Why: keep docs matching the new feature
    - How: updated feature lists, the structure breakdown, the hardware pin table + BOM, and the sim wiring/run steps
    - Benefit: docs and implementation agree again
2026-06-24 chore(sim): tidy diagram layout, set dimmers to 100/80/50/20%
    - What: cleaner part layout and pot values 1023/818/512/205 (= 100/80/50/20%)
    - Why: clearer demo of the four channels at distinct, recognizable levels
    - How: edited wokwi-potentiometer value attrs; layout repositioned
    - Benefit: the simulator opens with an obvious brightness spread across the four LED strips
2026-06-24 docs: correct stale unit-test count (10/10 -> 19/19)
    - What: updated the Status line in README.md and docs/README.md
    - Why: the count was stale; the suite grew to 19 cases after the palette/mode/button work
    - How: ran `pio test -e native` (19/19 passing) and synced both Status lines to match
    - Benefit: docs accurately reflect current test coverage
2026-06-24 docs(hardware): reformat BOM as a table and specify the dimmer pot
    - What: converted the BOM to a Qty/Component/Spec table, specified the dimmer as a standard single-turn rotary 10 kΩ linear (B10K) pot, and added a divider-wiring rule
    - Why: the BOM listed "potentiometer" with no type, leaving taper, resistance, and wiring ambiguous
    - How: pinned linear taper (curve is done in software) and 10 kΩ to keep ADC source impedance in spec; noted wiper-as-divider wiring
    - Benefit: the BOM is now buildable from as-is without guesswork on pot selection or wiring
2026-06-24 docs(application): spec the actual 35-LED WS2812 ring
    - What: replaced "WS2812 strip bent into a ring" with the pre-made 35-LED WS2812 ring (5 V, 5050 RGB, integrated drivers) and dropped the unverified translucent-cover detail
    - Why: the build now uses real ring boards, and stating an enclosure we don't have read as fact
    - How: described the actual part and noted the firmware sees a ring as 35 sequential pixels (shape is enclosure-only)
    - Benefit: the example build reflects the parts on hand without inventing details
2026-06-24 chore(sim): add the data-line series resistor to the diagram
    - What: inserted a 330 Ω resistor (r1) in series between nano D6 and ledStrip1 DIN, replacing the direct connection
    - Why: the sim should reflect the real wiring rule (~330-470 Ω at the first DIN) discussed for the hardware build
    - How: routed nano:6 -> r1:1 and r1:2 -> ledStrip1:DIN in the Wokwi diagram
    - Benefit: the simulation now matches the documented data-line protection, keeping sim and hardware consistent
